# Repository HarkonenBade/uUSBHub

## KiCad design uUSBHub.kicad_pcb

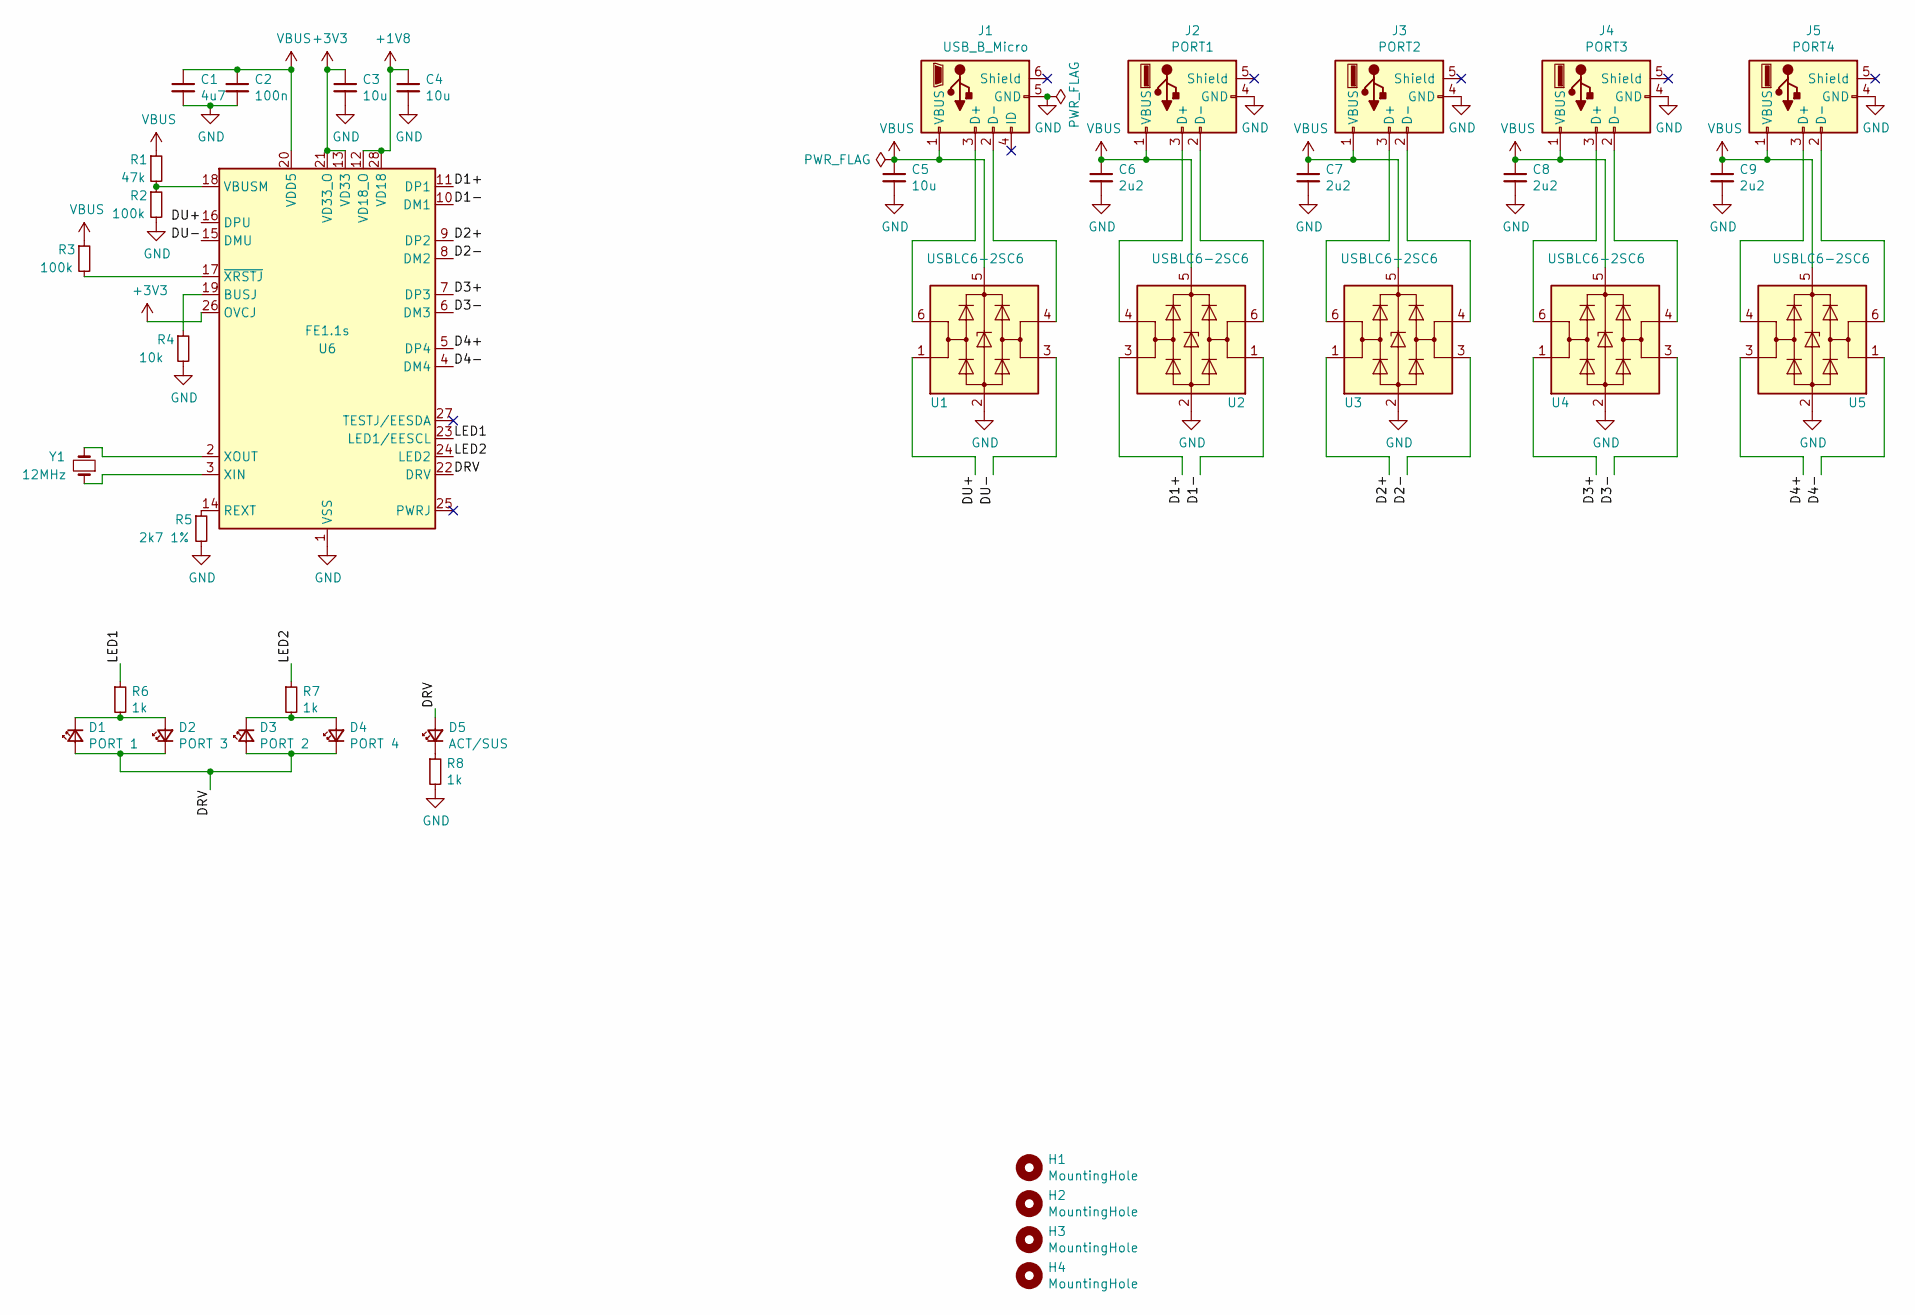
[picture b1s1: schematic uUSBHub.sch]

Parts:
C1: 4u7; C_0603_1608Metric
C2: 100n; C_0603_1608Metric
C3, C4, C5: 10u; C_0805_2012Metric
C6, C7, C8, C9: 2u2; C_0603_1608Metric
D1: PORT 1; LED_0805_2012Metric
D2: PORT 3; LED_0805_2012Metric
D3: PORT 2; LED_0805_2012Metric
D4: PORT 4; LED_0805_2012Metric
D5: ACT/SUS; LED_0805_2012Metric
H1, H2, H3, H4: MountingHole; MountingHole_3.2mm_M3_ISO14580
J1: USB_B_Micro; U254-051T-4BH83-F1S
J2: PORT1; JTJ-USB-AF-08
J3: PORT2; JTJ-USB-AF-08
J4: PORT3; JTJ-USB-AF-08
J5: PORT4; JTJ-USB-AF-08
R1: 47k; R_0603_1608Metric
R2, R3: 100k; R_0603_1608Metric
R4: 10k; R_0603_1608Metric
R5: 2k7 1%; R_0603_1608Metric
R6, R7, R8: 1k; R_0603_1608Metric
U1, U2, U3, U4, U5: USBLC6-2SC6; SOT-23-6
U6: FE1.1s; SSOP-28_3.9x9.9mm_P0.635mm
Y1: 12MHz

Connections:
+1V8: C4.1, U6.12 (VD18_O), U6.28 (VD18)
+3V3: C3.1, U6.13 (VD33), U6.21 (VD33_O), U6.26 (OVCJ)
/D1+: U2.3 (I/O2), U6.11 (DP1)
/D1-: U2.1 (I/O1), U6.10 (DM1)
/D2+: U3.1 (I/O1), U6.9 (DP2)
/D2-: U3.3 (I/O2), U6.8 (DM2)
/D3+: U4.1 (I/O1), U6.7 (DP3)
/D3-: U4.3 (I/O2), U6.6 (DM3)
/D4+: U5.3 (I/O2), U6.5 (DP4)
/D4-: U5.1 (I/O1), U6.4 (DM4)
/DRV: D1.2 (A), D2.1 (K), D3.2 (A), D4.1 (K), D5.2 (A), U6.22 (DRV)
/DU+: U1.1 (I/O1), U6.16 (DPU)
/DU-: U1.3 (I/O2), U6.15 (DMU)
/LED1: R6.1, U6.23 (LED1/EESCL)
/LED2: R7.1, U6.24 (LED2)
GND: C1.2, C2.2, C3.2, C4.2, C5.2, C6.2, C7.2, C8.2, C9.2, J1.5 (GND), J2.4 (GND), J3.4 (GND), J4.4 (GND), J5.4 (GND), R2.2, R4.2, R5.2, R8.2, U1.2 (GND), U2.2 (GND), U3.2 (GND), U4.2 (GND), U5.2 (GND), U6.1 (VSS)
unnamed: D1.1 (K), D2.2 (A), R6.2
unnamed: D3.1 (K), D4.2 (A), R7.2
unnamed: D5.1 (K), R8.1
unnamed: J1.2 (D-), U1.4 (I/O2)
unnamed: J1.3 (D+), U1.6 (I/O1)
unnamed: J2.2 (D-), U2.6 (I/O1)
unnamed: J2.3 (D+), U2.4 (I/O2)
unnamed: J3.2 (D-), U3.4 (I/O2)
unnamed: J3.3 (D+), U3.6 (I/O1)
unnamed: J4.2 (D-), U4.4 (I/O2)
unnamed: J4.3 (D+), U4.6 (I/O1)
unnamed: J5.2 (D-), U5.6 (I/O1)
unnamed: J5.3 (D+), U5.4 (I/O2)
unnamed: R1.2, R2.1, U6.18 (VBUSM)
unnamed: R3.2, U6.17 (~XRSTJ)
unnamed: R4.1, U6.19 (BUSJ)
unnamed: R5.1, U6.14 (REXT)
unnamed: U6.3 (XIN), Y1.1
unnamed: U6.2 (XOUT), Y1.2
VBUS: C1.1, C2.1, C5.1, C6.1, C7.1, C8.1, C9.1, J1.1 (VBUS), J2.1 (VBUS), J3.1 (VBUS), J4.1 (VBUS), J5.1 (VBUS), R1.1, R3.1, U1.5 (VBUS), U2.5 (VBUS), U3.5 (VBUS), U4.5 (VBUS), U5.5 (VBUS), U6.20 (VDD5)

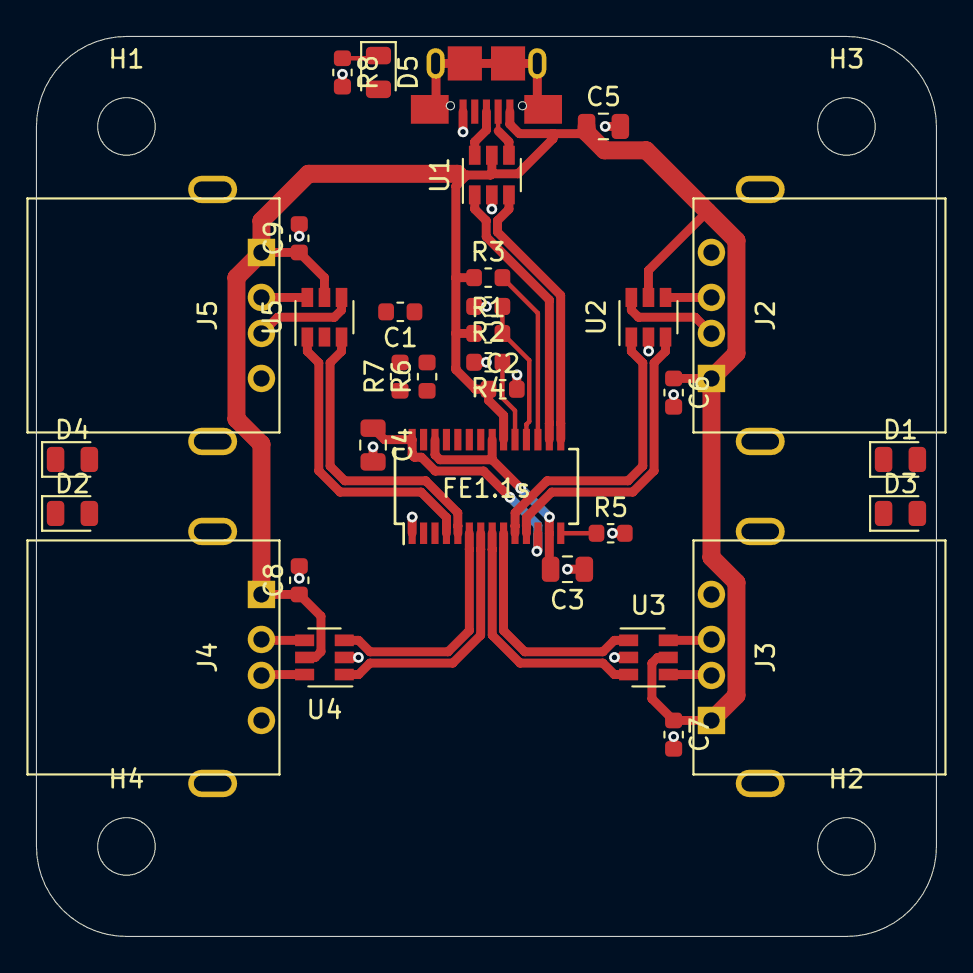
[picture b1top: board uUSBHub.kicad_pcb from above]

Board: 2 copper layers, 50.0 x 50.0 mm, 37 parts (0 on the bottom side), 34 nets.

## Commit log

2020-10-02 Create LICENSE
2020-10-02 Add main IC and ports with ESD
2020-10-03 Add indicator LEDs
2020-10-03 Mopping up remaining IC control pins
2020-10-03 Correct some extra pins bits, also add 5v decoupling
2020-10-03 Initial footprint assignment for header version
2020-10-04 Tweak the data line names to properly allow differential pair routing
